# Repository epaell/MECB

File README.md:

# MECB
A random assortment of software for the MECB system.

# 68008 tester
A simple free-running tester for PLCC 68008s

# SD-drive
Firmware for Arduino SD-drive based on Corsham Technologies SD-drive interface

# SDCardShield
KiCAD schematic and PCB for the MECB version of the SD-drive interface.

# MAME
Software for partially emulating the MECB 6502, 6809 and hypothetical Z80 and 68008 systems

# MECB_6502
Collection of software for the MECB_6502 system

# MECB_6809
Collection of software for the MECB_6809 system

# MECB_Z80
Test software for the hypothetical MECB_Z80 system (currently for testing emulation).

# MECB_68008
Test software for the MECB_68008 system (including a similar MAME board for testing).

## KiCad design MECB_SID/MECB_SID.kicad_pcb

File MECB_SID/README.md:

# MECB_SID
An implementation of a basic SID Interface for the MECB system. If only one SID is required only that half of the board needs to be populated.

The jumpers select different operating modes depending on your system. For systems with a 1 MHz system clock the clock from the MECB bus can be used to drive the SID. Under such circumstances it is also possible to pass the address lines directly to the SID chip. With the PLD set up for this mode (default) addressing the first SID is at $A0-$BF and the second SID is at $D0-$EF. This has been tested with the MECB 68008 running at 10 MHz (as this generates a 1 MHz system clock) and the MECB 6502 with a 1 MHz clock (which also provides the 1 MHz system clock). Some sample programs are available in the MECB_6502 area of this repository.

For higher clock rate systems a 1 MHz crystal can be installed and the jumper selected to use this clock in place of the system clock. Under this setup, the SID chip likely can't be addressed directly and so the onboard latch is used to hold the address of the register. With the PLD set up appropriately, writing to $A0 selects the SID register to work with, writing to $A1 writes to the selected register on the first SID and writing to $A2 writes to the selected register on the second SID. NOTE: this mode is yet to be tested. Testing is also needed to see how high a CPU clock this can operate at.

Note: The audio input section hasn't been tested either.

WARNING: This design doesn't work with clocks greater than 1 MHz. A new design update will be needed to alleviate this issue (currently only the address of the register is buffered but the data going to the register also needs buffering).

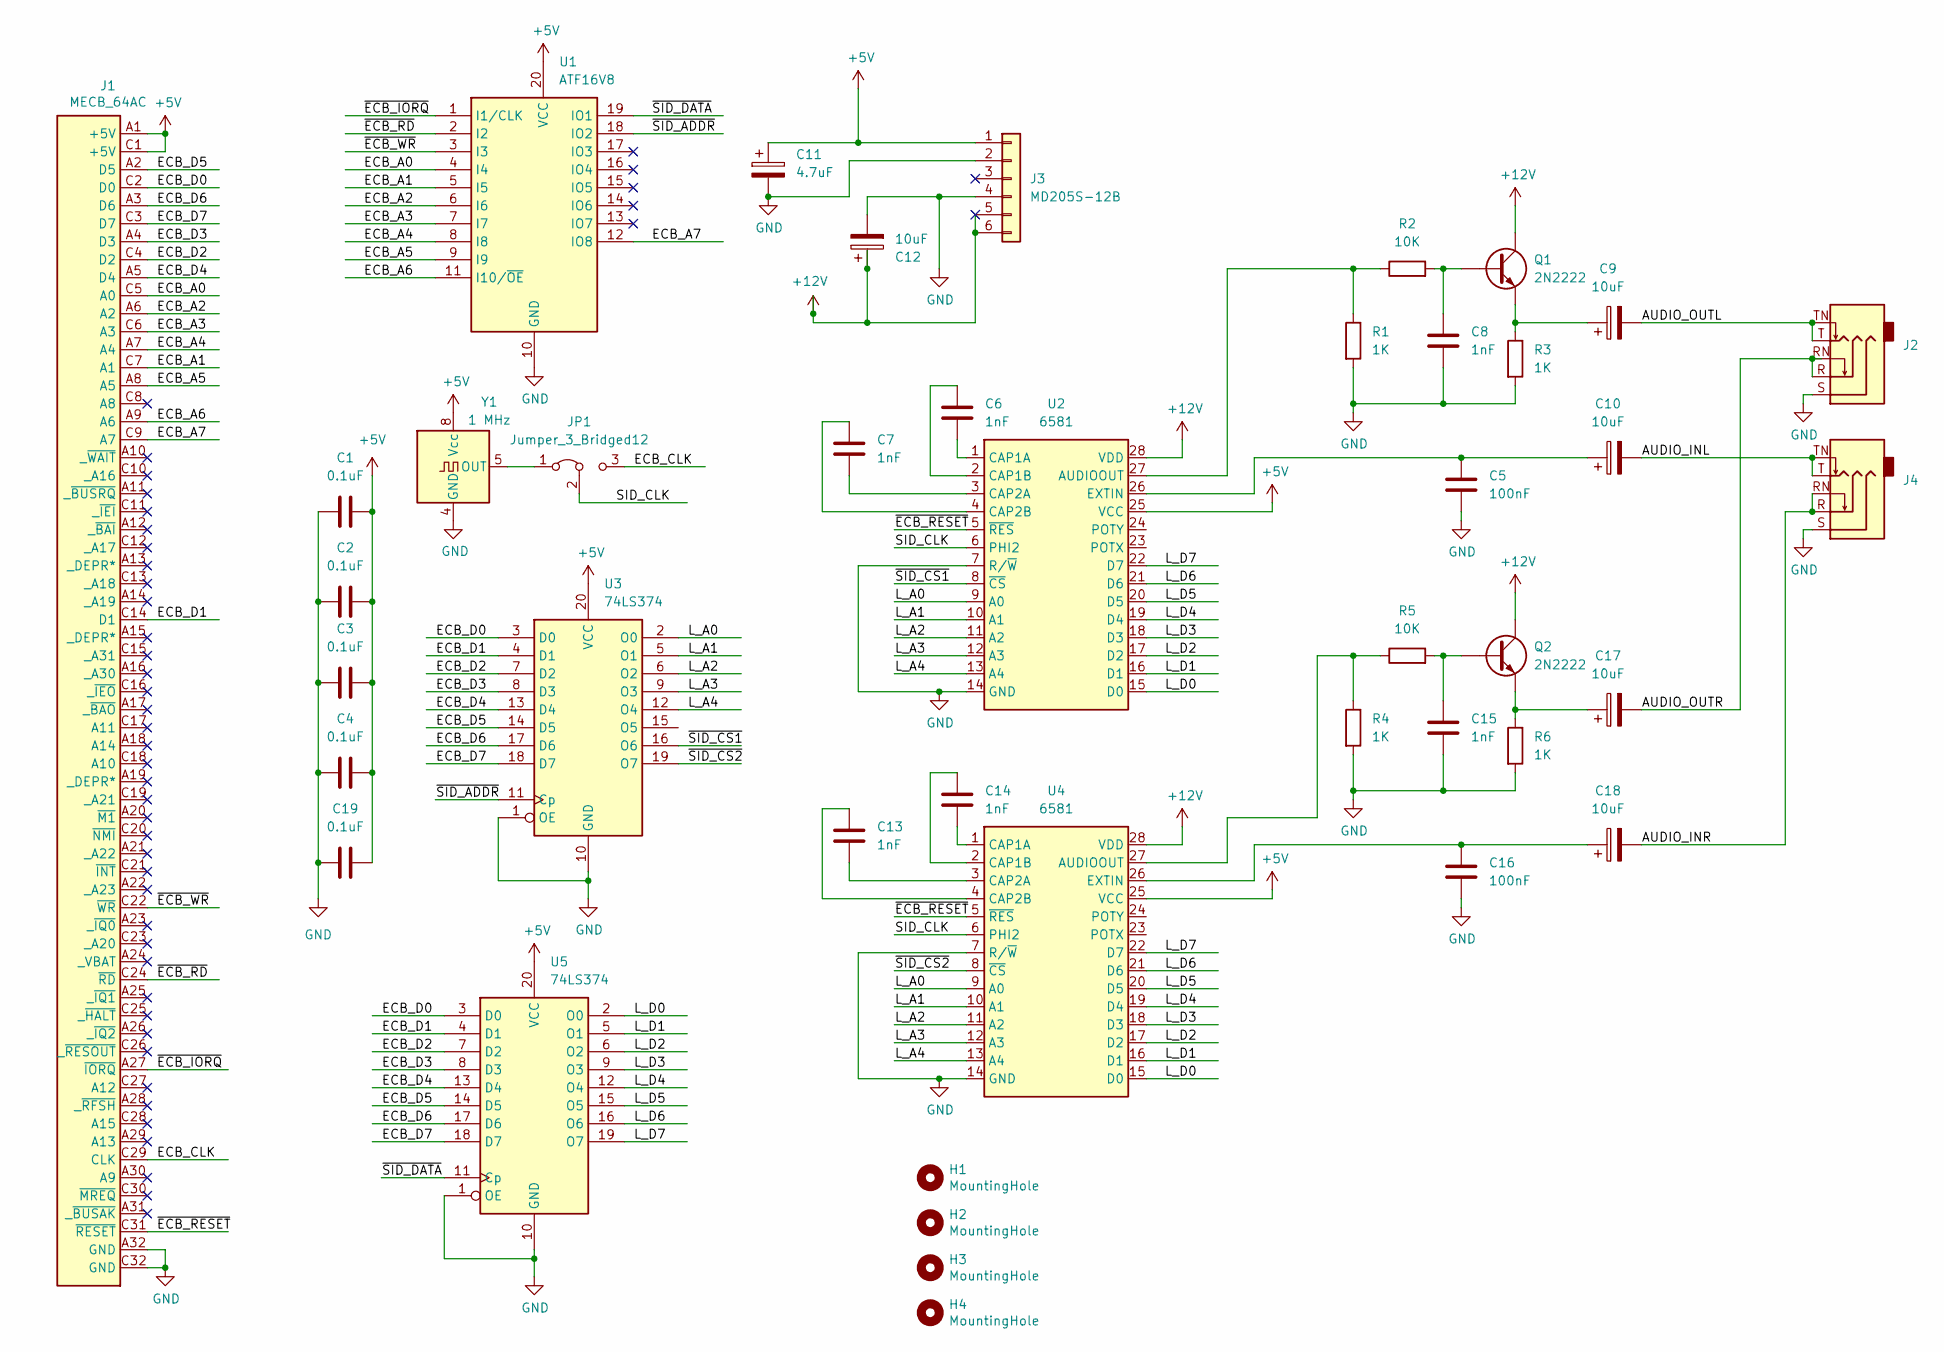
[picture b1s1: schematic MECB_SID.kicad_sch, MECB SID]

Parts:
C1, C2, C3, C4, C19: 0.1uF; C_Disc_D5.0mm_W2.5mm_P5.00mm
C5, C16: 100nF; C_Disc_D5.0mm_W2.5mm_P5.00mm
C6, C7, C8, C13, C14, C15: 1nF; C_Disc_D5.0mm_W2.5mm_P5.00mm
C9, C10, C12, C17, C18: 10uF; CP_Radial_D8.0mm_P3.50mm
C11: 4.7uF; CP_Radial_D8.0mm_P3.50mm
H1, H2, H3, H4: MountingHole; MountingHole_3.2mm_M3
J1: MECB_64AC; DIN41612_C_2x32_C64AC_Male_Horizontal_THT
J2, J4: AudioJack3_SwitchTR; Jack_3.5mm_CUI_SJ1-3525N_Horizontal
J3: MD205S-12B; PinHeader_1x06_P2.54mm_Vertical
JP1: Jumper_3_Bridged12; PinHeader_1x03_P2.54mm_Vertical
Q1, Q2: 2N2222; TO-92L_HandSolder
R1, R3, R4, R6: 1K; R_Axial_DIN0309_L9.0mm_D3.2mm_P12.70mm_Horizontal
R2, R5: 10K; R_Axial_DIN0309_L9.0mm_D3.2mm_P12.70mm_Horizontal
U1: ATF16V8; DIP-20_W7.62mm_Socket_LongPads; Mouser Part Number 556-AF22V10C15PU
U2, U4: 6581; DIP-28_W15.24mm_Socket_LongPads
U3, U5: 74LS374; DIP-20_W7.62mm_Socket_LongPads
Y1: 1 MHz; Oscillator_DIP-8_LargePads

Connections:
+5V: C1.2, C2.2, C3.2, C4.2, C11.1, C19.2, J1.A1 (+5V), J1.C1 (+5V), J3.1, U1.20 (VCC), U2.25 (VCC), U3.20 (VCC), U4.25 (VCC), U5.20 (VCC), Y1.8 (Vcc)
+12V: C12.1, J3.5, J3.6, Q1.C, Q2.C, U2.28 (VDD), U4.28 (VDD)
/AUDIO_INL: C10.2, J4.T, J4.TN
/AUDIO_INR: C18.2, J4.R, J4.RN
/AUDIO_OUTL: C9.2, J2.T, J2.TN
/AUDIO_OUTR: C17.2, J2.R, J2.RN
/ECB_A0: J1.C5 (A0), U1.4 (I4)
/ECB_A1: J1.C7 (A1), U1.5 (I5)
/ECB_A2: J1.A6 (A2), U1.6 (I6)
/ECB_A3: J1.C6 (A3), U1.7 (I7)
/ECB_A4: J1.A7 (A4), U1.8 (I8)
/ECB_A5: J1.A8 (A5), U1.9 (I9)
/ECB_A6: J1.A9 (A6), U1.11 (I10/~OE)
/ECB_A7: J1.C9 (A7), U1.12 (IO8)
/ECB_CLK: J1.C29 (CLK), JP1.3 (B)
/ECB_D0: J1.C2 (D0), U3.3 (D0), U5.3 (D0)
/ECB_D1: J1.C14 (D1), U3.4 (D1), U5.4 (D1)
/ECB_D2: J1.C4 (D2), U3.7 (D2), U5.7 (D2)
/ECB_D3: J1.A4 (D3), U3.8 (D3), U5.8 (D3)
/ECB_D4: J1.A5 (D4), U3.13 (D4), U5.13 (D4)
/ECB_D5: J1.A2 (D5), U3.14 (D5), U5.14 (D5)
/ECB_D6: J1.A3 (D6), U3.17 (D6), U5.17 (D6)
/ECB_D7: J1.C3 (D7), U3.18 (D7), U5.18 (D7)
/L_A0: U2.9 (A0), U3.2 (O0), U4.9 (A0)
/L_A1: U2.10 (A1), U3.5 (O1), U4.10 (A1)
/L_A2: U2.11 (A2), U3.6 (O2), U4.11 (A2)
/L_A3: U2.12 (A3), U3.9 (O3), U4.12 (A3)
/L_A4: U2.13 (A4), U3.12 (O4), U4.13 (A4)
/L_D0: U2.15 (D0), U4.15 (D0), U5.2 (O0)
/L_D1: U2.16 (D1), U4.16 (D1), U5.5 (O1)
/L_D2: U2.17 (D2), U4.17 (D2), U5.6 (O2)
/L_D3: U2.18 (D3), U4.18 (D3), U5.9 (O3)
/L_D4: U2.19 (D4), U4.19 (D4), U5.12 (O4)
/L_D5: U2.20 (D5), U4.20 (D5), U5.15 (O5)
/L_D6: U2.21 (D6), U4.21 (D6), U5.16 (O6)
/L_D7: U2.22 (D7), U4.22 (D7), U5.19 (O7)
/SID_CLK: JP1.2 (C), U2.6 (PHI2), U4.6 (PHI2)
/~ECB_IORQ: J1.A27 (~IORQ), U1.1 (I1/CLK)
/~ECB_RD: J1.C24 (~RD), U1.2 (I2)
/~ECB_RESET: J1.C31 (~RESET), U2.5 (~RES), U4.5 (~RES)
/~ECB_WR: J1.C22 (~WR), U1.3 (I3)
/~SID_ADDR: U1.18 (IO2), U3.11 (Cp)
/~SID_CS1: U2.8 (~CS), U3.16 (O6)
/~SID_CS2: U3.19 (O7), U4.8 (~CS)
/~SID_DATA: U1.19 (IO1), U5.11 (Cp)
GND: C1.1, C2.1, C3.1, C4.1, C5.2, C8.2, C11.2, C12.2, C15.2, C16.2, C19.1, J1.A32 (GND), J1.C32 (GND), J2.S, J3.2, J3.4, J4.S, R1.2, R3.2, R4.2, R6.2, U1.10 (GND), U2.7 (R/~W), U2.14 (GND), U3.1 (OE), U3.10 (GND), U4.7 (R/~W), U4.14 (GND), U5.1 (OE), U5.10 (GND), Y1.4 (GND)
unnamed: C8.1, Q1.B, R2.2
unnamed: C9.1, Q1.E, R3.1
unnamed: C15.1, Q2.B, R5.2
unnamed: C17.1, Q2.E, R6.1
unnamed: JP1.1 (A), Y1.5 (OUT)
unnamed: R1.1, R2.1, U2.27 (AUDIOOUT)
unnamed: C6.1, U2.1 (CAP1A)
unnamed: C6.2, U2.2 (CAP1B)
unnamed: C7.1, U2.3 (CAP2A)
unnamed: C7.2, U2.4 (CAP2B)
unnamed: C5.1, C10.1, U2.26 (EXTIN)
unnamed: R4.1, R5.1, U4.27 (AUDIOOUT)
unnamed: C14.1, U4.1 (CAP1A)
unnamed: C14.2, U4.2 (CAP1B)
unnamed: C13.1, U4.3 (CAP2A)
unnamed: C13.2, U4.4 (CAP2B)
unnamed: C16.1, C18.1, U4.26 (EXTIN)

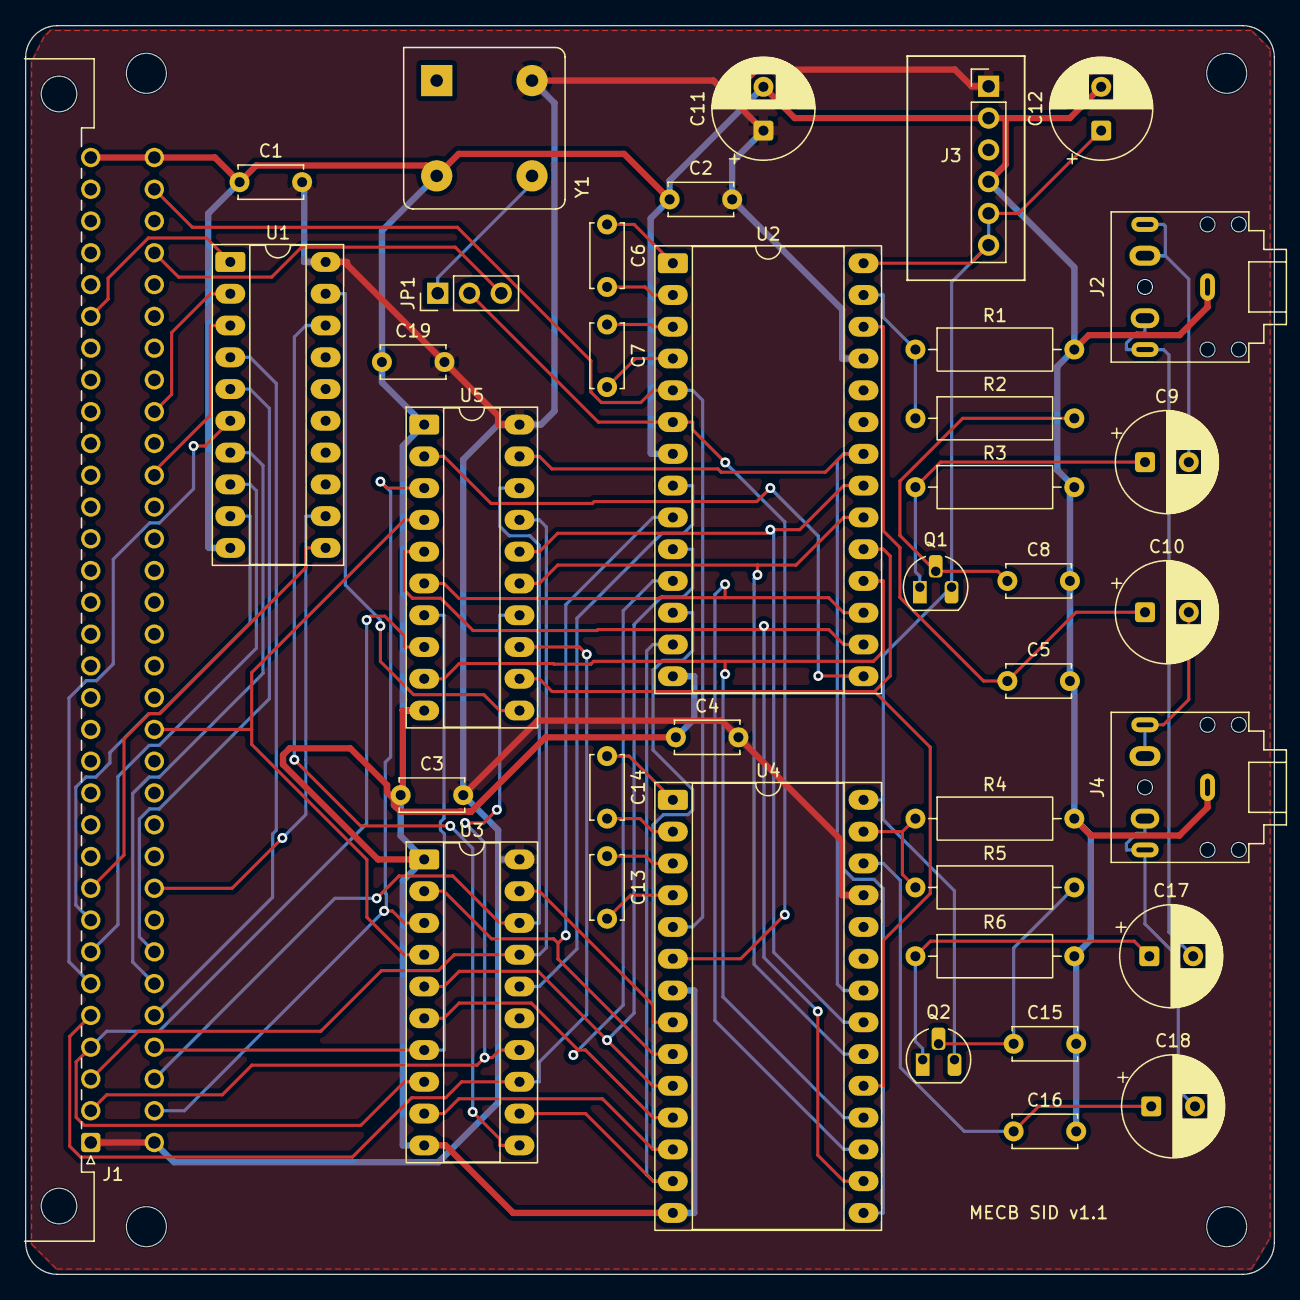
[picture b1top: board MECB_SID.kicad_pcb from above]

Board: 2 copper layers, 99.8 x 99.8 mm, 42 parts (0 on the bottom side), 63 nets.

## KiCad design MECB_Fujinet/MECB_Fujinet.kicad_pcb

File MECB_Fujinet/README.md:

# MECB Fujinet Board
An implementation of a Fujinet board for the MECB system. The hardware is based on a preliminary RC2014 Fujinet interface (https://github.com/FujiNetWIFI/fujinet-hardware/tree/master/RC2014/rev-0.3) that is still under development. The PLD is set to select the device at port $C2 (or $XXC2 on the MECB memory map if used with CPUs without a separate I/O map).

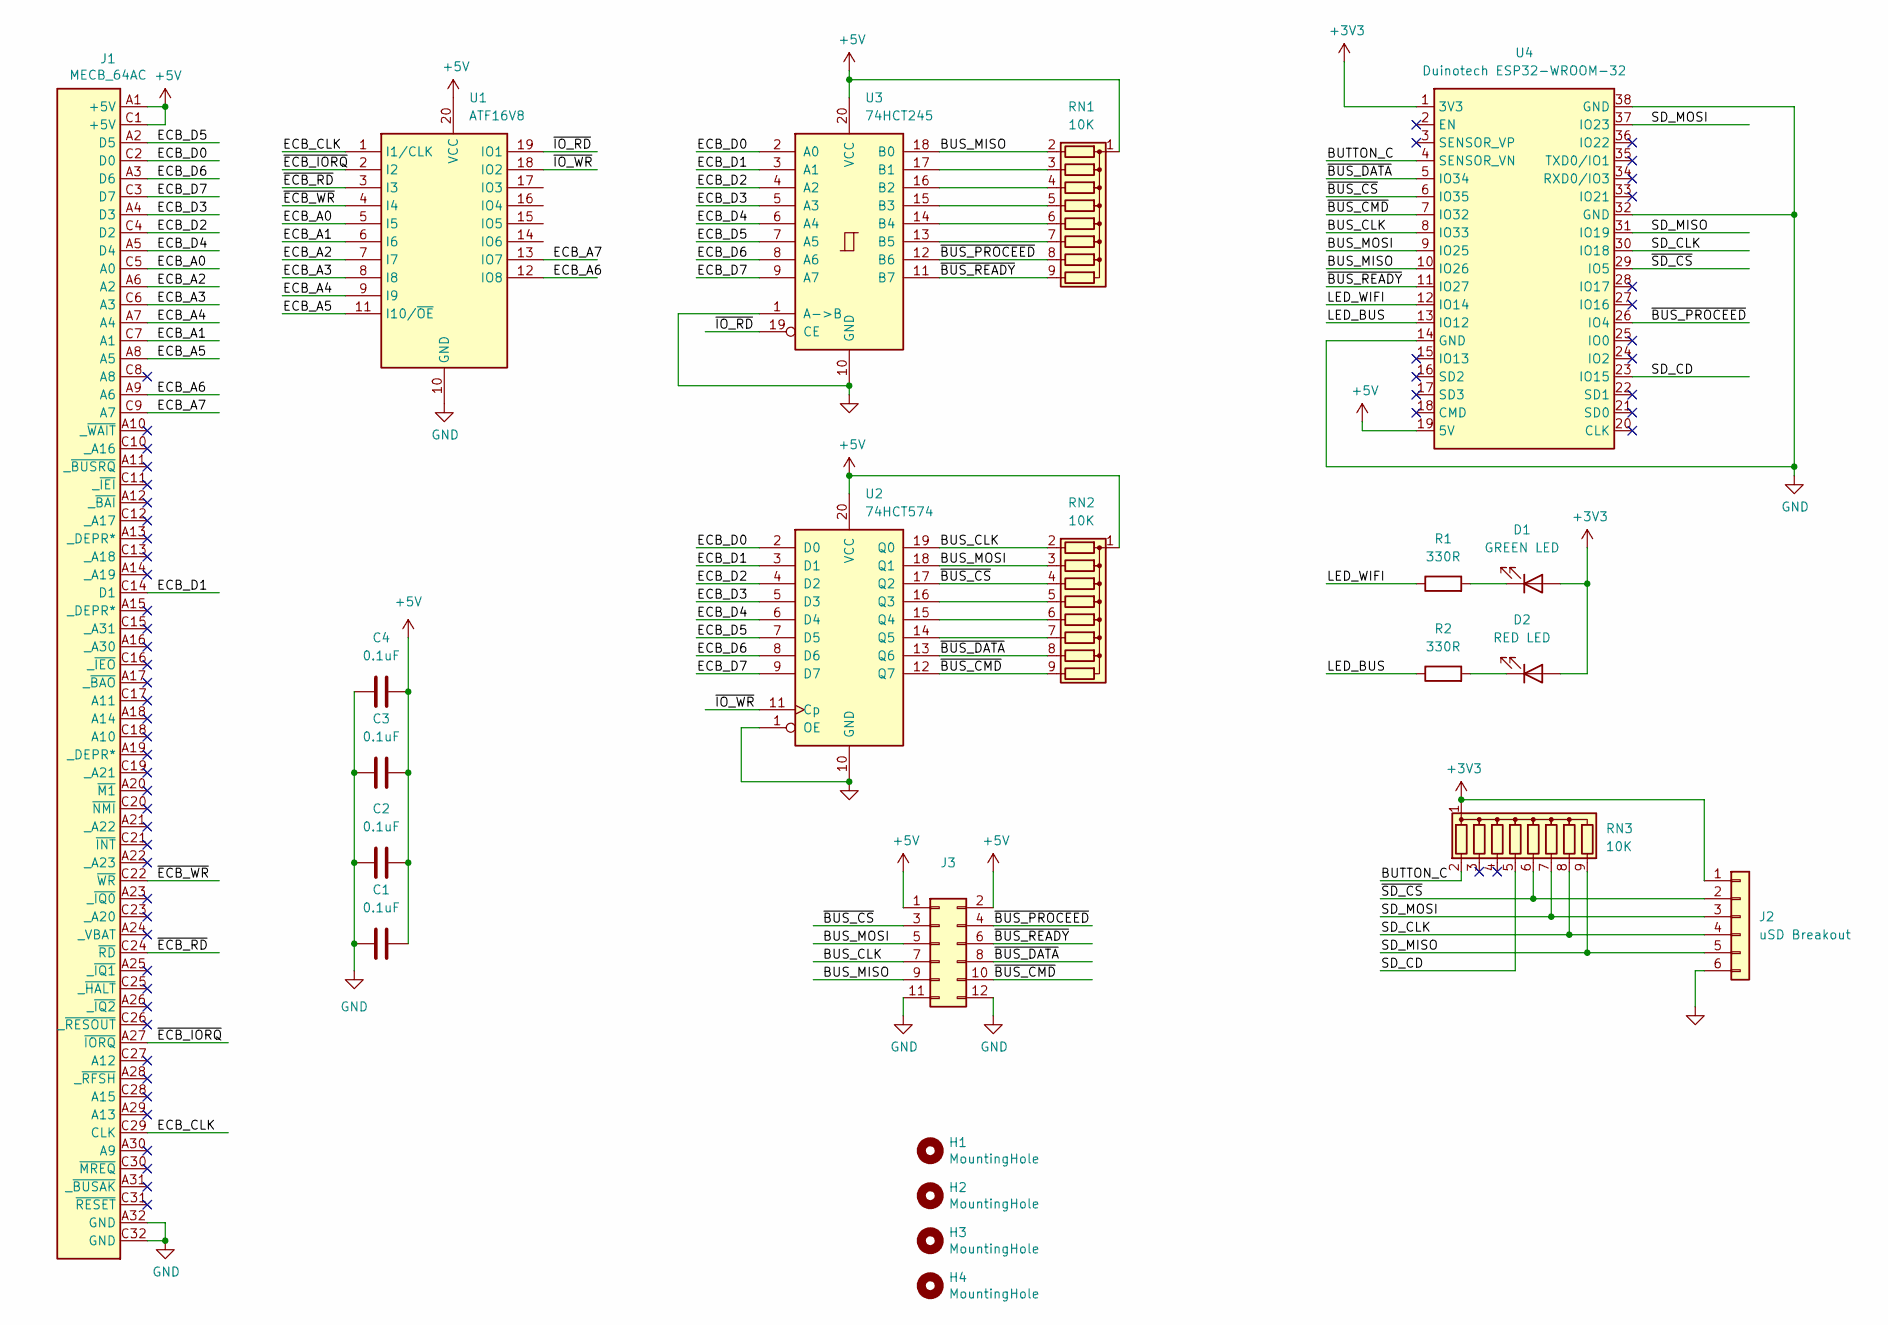
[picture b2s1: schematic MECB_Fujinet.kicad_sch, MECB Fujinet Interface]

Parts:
C1, C2, C3, C4: 0.1uF; C_Disc_D5.0mm_W2.5mm_P5.00mm
D1: GREEN LED; LED_D3.0mm_Horizontal_O1.27mm_Z2.0mm
D2: RED LED; LED_D3.0mm_Horizontal_O1.27mm_Z2.0mm
H1, H2, H3, H4: MountingHole; MountingHole_3.2mm_M3
J1: MECB_64AC; DIN41612_C_2x32_C64AC_Male_Horizontal_THT
J2: uSD Breakout; PinHeader_1x06_P2.54mm_Horizontal
J3: Conn_02x06_Odd_Even; IDC-Header_2x06_P2.54mm_Vertical
R1, R2: 330R; R_Axial_DIN0309_L9.0mm_D3.2mm_P12.70mm_Horizontal
RN1, RN2, RN3: 10K; R_Array_SIP9
U1: ATF16V8; DIP-20_W7.62mm_Socket_LongPads; Mouser Part Number 556-AF22V10C15PU
U2: 74HCT574; DIP-20_W7.62mm_Socket_LongPads
U3: 74HCT245; DIP-20_W7.62mm_Socket_LongPads
U4: Duinotech ESP32-WROOM-32; DIP-38_Socket_LongPads

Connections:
+3V3: D1.2 (A), D2.2 (A), J2.1, RN3.1 (common), U4.1 (3V3)
+5V: C1.2, C2.2, C3.2, C4.2, J1.A1 (+5V), J1.C1 (+5V), J3.1, J3.2, RN1.1 (common), RN2.1 (common), U1.20 (VCC), U2.20 (VCC), U3.20 (VCC), U4.19 (5V)
/BUS_CLK: J3.7, RN2.2 (R1), U2.19 (Q0), U4.8 (IO33)
/BUS_MISO: J3.9, RN1.2 (R1), U3.18 (B0), U4.10 (IO26)
/BUS_MOSI: J3.5, RN2.3 (R2), U2.18 (Q1), U4.9 (IO25)
/BUTTON_C: RN3.2 (R1), U4.4 (SENSOR_VN)
/ECB_A0: J1.C5 (A0), U1.5 (I5)
/ECB_A1: J1.C7 (A1), U1.6 (I6)
/ECB_A2: J1.A6 (A2), U1.7 (I7)
/ECB_A3: J1.C6 (A3), U1.8 (I8)
/ECB_A4: J1.A7 (A4), U1.9 (I9)
/ECB_A5: J1.A8 (A5), U1.11 (I10/~OE)
/ECB_A6: J1.A9 (A6), U1.12 (IO8)
/ECB_A7: J1.C9 (A7), U1.13 (IO7)
/ECB_CLK: J1.C29 (CLK), U1.1 (I1/CLK)
/ECB_D0: J1.C2 (D0), U2.2 (D0), U3.2 (A0)
/ECB_D1: J1.C14 (D1), U2.3 (D1), U3.3 (A1)
/ECB_D2: J1.C4 (D2), U2.4 (D2), U3.4 (A2)
/ECB_D3: J1.A4 (D3), U2.5 (D3), U3.5 (A3)
/ECB_D4: J1.A5 (D4), U2.6 (D4), U3.6 (A4)
/ECB_D5: J1.A2 (D5), U2.7 (D5), U3.7 (A5)
/ECB_D6: J1.A3 (D6), U2.8 (D6), U3.8 (A6)
/ECB_D7: J1.C3 (D7), U2.9 (D7), U3.9 (A7)
/LED_BUS: R2.1, U4.13 (IO12)
/LED_WIFI: R1.1, U4.12 (IO14)
/SD_CD: RN3.5 (R4), U4.23 (IO15)
/SD_CLK: J2.4, RN3.8 (R7), U4.30 (IO18)
/SD_MISO: J2.5, RN3.9 (R8), U4.31 (IO19)
/SD_MOSI: J2.3, RN3.7 (R6), U4.37 (IO23)
/~BUS_CMD: J3.10, RN2.9 (R8), U2.12 (Q7), U4.7 (IO32)
/~BUS_CS: J3.3, RN2.4 (R3), U2.17 (Q2), U4.6 (IO35)
/~BUS_DATA: J3.8, RN2.8 (R7), U2.13 (Q6), U4.5 (IO34)
/~BUS_PROCEED: J3.4, RN1.8 (R7), U3.12 (B6), U4.26 (IO4)
/~BUS_READY: J3.6, RN1.9 (R8), U3.11 (B7), U4.11 (IO27)
/~ECB_IORQ: J1.A27 (~IORQ), U1.2 (I2)
/~ECB_RD: J1.C24 (~RD), U1.3 (I3)
/~ECB_WR: J1.C22 (~WR), U1.4 (I4)
/~IO_RD: U1.19 (IO1), U3.19 (CE)
/~IO_WR: U1.18 (IO2), U2.11 (Cp)
/~SD_CS: J2.2, RN3.6 (R5), U4.29 (IO5)
GND: C1.1, C2.1, C3.1, C4.1, J1.A32 (GND), J1.C32 (GND), J2.6, J3.11, J3.12, U1.10 (GND), U2.1 (OE), U2.10 (GND), U3.1 (A->B), U3.10 (GND), U4.14 (GND), U4.32 (GND), U4.38 (GND)
unnamed: D1.1 (K), R1.2
unnamed: D2.1 (K), R2.2
unnamed: RN1.3 (R2), U3.17 (B1)
unnamed: RN1.4 (R3), U3.16 (B2)
unnamed: RN1.5 (R4), U3.15 (B3)
unnamed: RN1.6 (R5), U3.14 (B4)
unnamed: RN1.7 (R6), U3.13 (B5)
unnamed: RN2.5 (R4), U2.16 (Q3)
unnamed: RN2.6 (R5), U2.15 (Q4)
unnamed: RN2.7 (R6), U2.14 (Q5)

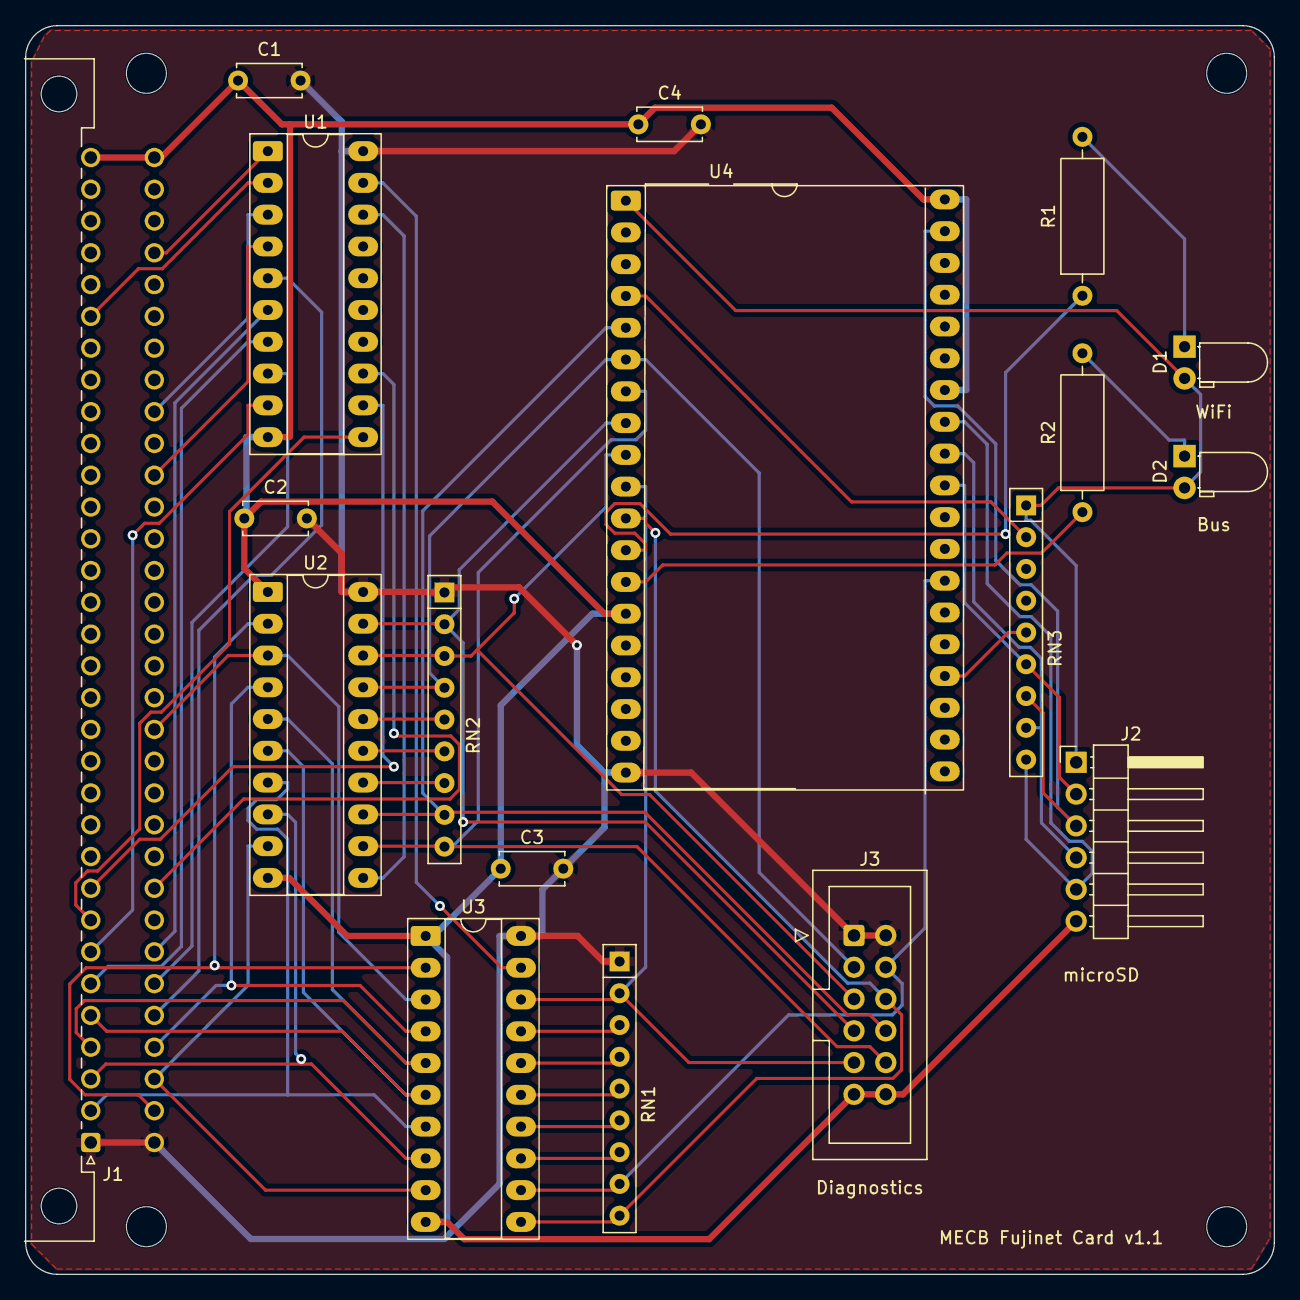
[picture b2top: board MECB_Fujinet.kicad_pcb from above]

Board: 2 copper layers, 99.8 x 99.8 mm, 22 parts (0 on the bottom side), 51 nets.

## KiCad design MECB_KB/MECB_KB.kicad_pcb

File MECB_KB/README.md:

# MECB_KB
An implementation of a PS/2 Keyboard/Mouse interface for the MECB system. The hardware is based on a similar design available for the RC2014 system (https://hackaday.io/project/184729-smart-ps2-keyboardmouse-for-rc2014).

I have confirmed that the V1.0 version of the KB board appears to be fully operational with MECB and RomWBW. By default, the PLD sets the address of the board registers to $60 and $64 (to maintain compatibility with RomWBW).

Note that this board requires the VIA VT82C64 - I have tried with other versions of the 8264 an the board does not work with those (I'm not 100% certain why but it seems like the firmware might be incompatible).

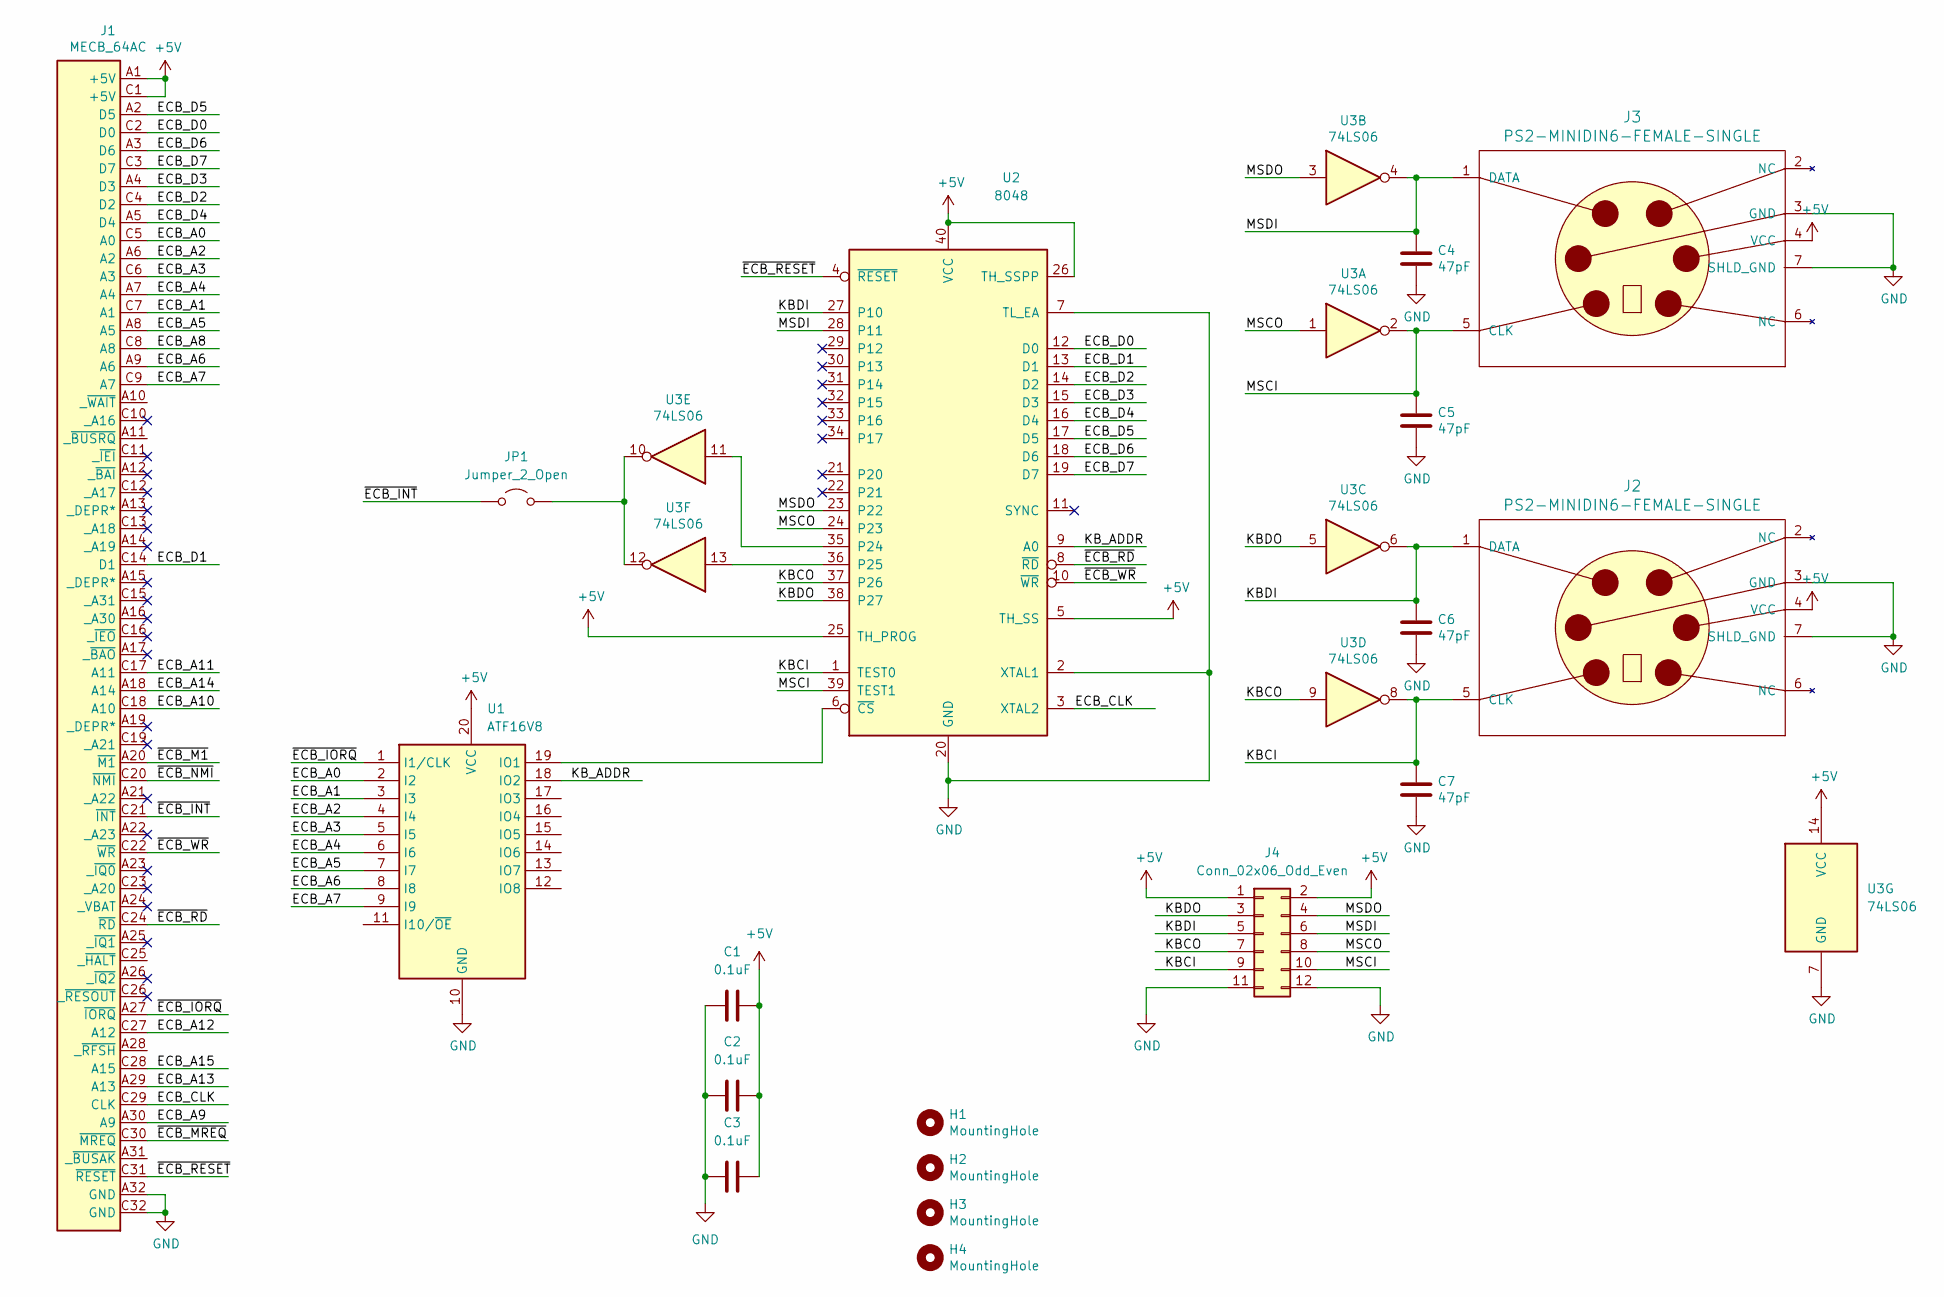
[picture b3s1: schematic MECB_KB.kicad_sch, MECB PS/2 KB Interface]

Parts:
C1, C2, C3: 0.1uF; C_Disc_D5.0mm_W2.5mm_P5.00mm
C4, C5, C6, C7: 47pF; C_Disc_D7.5mm_W5.0mm_P7.50mm
H1, H2, H3, H4: MountingHole; MountingHole_3.2mm_M3
J1: MECB_64AC; DIN41612_C_2x32_C64AC_Male_Horizontal_THT
J2, J3: PS2-MINIDIN6-FEMALE-SINGLE; MINI-DIN-6-FULL-SHIELD
J4: Conn_02x06_Odd_Even; PinHeader_2x06_P2.54mm_Vertical
JP1: Jumper_2_Open; PinHeader_1x02_P2.54mm_Vertical
U1: ATF16V8; DIP-20_W7.62mm_Socket_LongPads; Mouser Part Number 556-AF22V10C15PU
U2: 8048; DIP-40_W15.24mm_Socket_LongPads
U3: 74LS06; DIP-14_W7.62mm_Socket_LongPads

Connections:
+5V: C1.2, C2.2, C3.2, J1.A1 (+5V), J1.C1 (+5V), J2.4 (VCC), J3.4 (VCC), J4.1, J4.2, U1.20 (VCC), U2.5 (TH_SS), U2.25 (TH_PROG), U2.26 (TH_SSPP), U2.40 (VCC), U3.14 (VCC)
/ECB_A0: J1.C5 (A0), U1.2 (I2)
/ECB_A1: J1.C7 (A1), U1.3 (I3)
/ECB_A2: J1.A6 (A2), U1.4 (I4)
/ECB_A3: J1.C6 (A3), U1.5 (I5)
/ECB_A4: J1.A7 (A4), U1.6 (I6)
/ECB_A5: J1.A8 (A5), U1.7 (I7)
/ECB_A6: J1.A9 (A6), U1.8 (I8)
/ECB_A7: J1.C9 (A7), U1.9 (I9)
/ECB_A8: J1.C8 (A8)
/ECB_A9: J1.A30 (A9)
/ECB_A10: J1.C18 (A10)
/ECB_A11: J1.C17 (A11)
/ECB_A12: J1.C27 (A12)
/ECB_A13: J1.A29 (A13)
/ECB_A14: J1.A18 (A14)
/ECB_A15: J1.C28 (A15)
/ECB_CLK: J1.C29 (CLK), U2.3 (XTAL2)
/ECB_D0: J1.C2 (D0), U2.12 (D0)
/ECB_D1: J1.C14 (D1), U2.13 (D1)
/ECB_D2: J1.C4 (D2), U2.14 (D2)
/ECB_D3: J1.A4 (D3), U2.15 (D3)
/ECB_D4: J1.A5 (D4), U2.16 (D4)
/ECB_D5: J1.A2 (D5), U2.17 (D5)
/ECB_D6: J1.A3 (D6), U2.18 (D6)
/ECB_D7: J1.C3 (D7), U2.19 (D7)
/KBCI: C7.1, J2.5 (CLK), J4.9, U2.1 (TEST0), U3.8
/KBCO: J4.7, U2.37 (P26), U3.9
/KBDI: C6.1, J2.1 (DATA), J4.5, U2.27 (P10), U3.6
/KBDO: J4.3, U2.38 (P27), U3.5
/KB_ADDR: U1.18 (IO2), U2.9 (A0)
/MSCI: C5.1, J3.5 (CLK), J4.10, U2.39 (TEST1), U3.2
/MSCO: J4.8, U2.24 (P23), U3.1
/MSDI: C4.1, J3.1 (DATA), J4.6, U2.28 (P11), U3.4
/MSDO: J4.4, U2.23 (P22), U3.3
/~ECB_INT: J1.C21 (~INT), JP1.1 (A)
/~ECB_IORQ: J1.A27 (~IORQ), U1.1 (I1/CLK)
/~ECB_M1: J1.A20 (~M1)
/~ECB_MREQ: J1.C30 (~MREQ)
/~ECB_NMI: J1.C20 (~NMI)
/~ECB_RD: J1.C24 (~RD), U2.8 (~RD)
/~ECB_RESET: J1.C31 (~RESET), U2.4 (~RESET)
/~ECB_WR: J1.C22 (~WR), U2.10 (~WR)
GND: C1.1, C2.1, C3.1, C4.2, C5.2, C6.2, C7.2, J1.A32 (GND), J1.C32 (GND), J2.3 (GND), J2.7 (SHLD_GND), J3.3 (GND), J3.7 (SHLD_GND), J4.11, J4.12, U1.10 (GND), U2.2 (XTAL1), U2.7 (TL_EA), U2.20 (GND), U3.7 (GND)
unnamed: JP1.2 (B), U3.10, U3.12
unnamed: U1.19 (IO1), U2.6 (~CS)
unnamed: U2.35 (P24), U3.11
unnamed: U2.36 (P25), U3.13

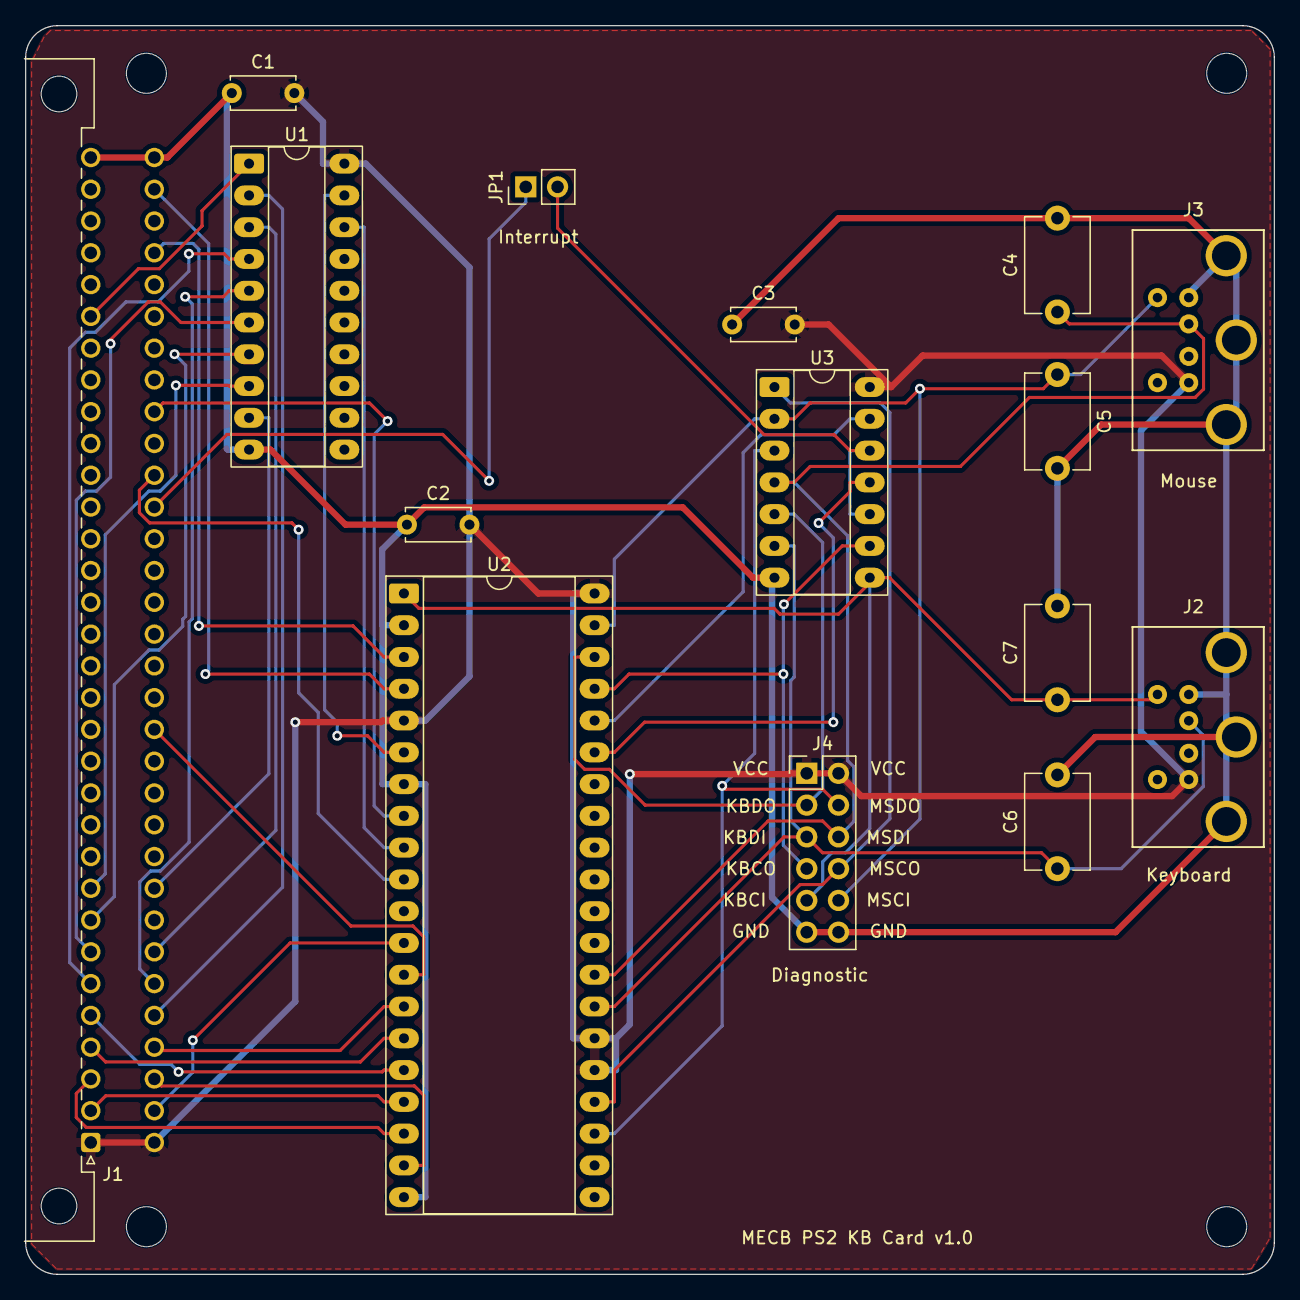
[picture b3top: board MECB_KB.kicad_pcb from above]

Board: 2 copper layers, 99.8 x 99.8 mm, 19 parts (0 on the bottom side), 37 nets.
